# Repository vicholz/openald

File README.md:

# OpenALD v1.0

**OpenALD** is an open, rechargeable pocket FM radio: an ATmega328PB + RDA5807M (RRD-102 module) board that runs from one
18650 cell, charges and programs over USB-C, and lives in a 3D-printed 31.9 × 89.75 × 33.86 mm case (35.9 wide at its dock collar). The repo also
holds an **Adafruit Feather RP2040 variant** built from off-the-shelf boards, a printed **18650 case for the stock MI03
pocket radio**, and a **6-slot USB-C PD charging dock**. Since t116u (2026-11-24) the single-board and Feather radios share one dock interface: a
35.9 × 33.86 mm end footprint (t122u; was 31.9) with the **USB-C in the bottom end face, centred across the width, 6.62 mm behind the
front face, mouth 1.0 mm inside**. They stand upright in any dock pocket; **the MI03 keeps its side USB-C and is not
dock-compatible**. Everything is KiCad 9 + OpenSCAD, generated by Python scripts.

> **Status: designed, CAD- and datasheet-checked, NOT built and NOT hardware-validated.** ERC/DRC, the JLC placement
> check and the 3D case-fit checks pass, but no board has been built, powered or programmed. The only firmware is the Feather variant's Arduino sketch, which compiles but has never run on hardware; the single board still has none.
> Treat the first build of each part as a prototype (see the bring-up checklist in [HANDOFF.md](HANDOFF.md#8-hardware-bring-up-test-checklist)).

**Picking this up later (person or AI)? Start with [HANDOFF.md](HANDOFF.md)**: full design history, decisions, hard
constraints, open TODOs, test checklist and exact regeneration commands.

| Folder | What it is | Status |
|---|---|---|
| [`radio_single_board/`](radio_single_board/README.md) | **OpenALD v1.0** single-board radio: ATmega328PB + RDA5807M, CH340K USB-C programming, TP4056 ~900 mA charging with DW01A/FS8205A protection and reverse-cell protection, thumbwheel (press = battery check), slide switch, 3-LED level bar. **26.9 × 84.75 mm 2-layer PCB**; case **31.9 × 89.75 × 33.86 mm** (35.9-wide dock collar on its lowest 27 mm), USB-C centred in the bottom end | Designed; ERC/DRC/JLC-CPL/case fit pass; not built |
| [`charging_dock/`](charging_dock/README.md) | **OpenALD Dock v1.0**: 6 radios stand upright on their bottom-end USB-C in pockets recessed 25 mm into a flat top (3 × 2 aligned grid, 1 in apart, LED sight windows), any mix of single-board / Feather radios (**not the MI03**); one rear USB-C PD input (≥ 45 W charger, 15 V or 20 V); HUSB238 + 2 × SY8205 bucks + SY6280 limit per slot. **170.5 × 112.6 × 37.3 mm** (fits a 220 × 180 bed) | Designed; ERC/DRC/JLC-CPL/fit pass; not built |
| [`radio_adafruit_feather_rp2040/`](radio_adafruit_feather_rp2040/README.md) | **OpenALD Feather RP2040 v1.0**: Feather RP2040 + 27.25 mm FM module with jack + 18650 holder; **no PCB**: SIQ-02FVS3 wheel glued into a deck cradle, heat-staked SS-12F16 switch, FM module flipped on pegged standoffs, the Feather's own USB-C (bottom end) as the dock port, its CHG / red / NeoPixel LEDs visible through front-face holes, all hand-wired. Case **35.9 × 98.71 × 33.86 mm**, same dock interface as the single board | Designed; fit check pass; FM-module header/jack details assumed; not built |
| [`mi03_case/`](mi03_case/README.md) | 18650 case for the stock MI03 FM pocket radio, **27.5 × 89.75 × 34.83 mm**, USB-C on the left long side. **Not dock-compatible** | CAD only; fit check pass; not printed |

Dock ↔ radio mechanical contract: [`charging_dock/DOCK_INTERFACE.md`](charging_dock/DOCK_INTERFACE.md).

**Part colours (t124u):** every case family has its own hue so parts are easy to tell apart: single board **blues**,
Feather **greens**, MI03 **oranges / reds**, dock **purples** (legend in each README; `tools/palette.py`). Each case
also has a **coloured 3MF plate** next to its STLs (`*_colored.3mf`, one named, coloured object per part).
## Quick links
* Single-board radio: [Gerbers](radio_single_board/fab/openald-gerbers-jlcpcb.zip) · [JLC BOM](radio_single_board/fab/openald-BOM-jlcpcb.csv) · [JLC CPL](radio_single_board/fab/openald-CPL-jlcpcb.csv) · [human BOM](radio_single_board/fab/openald-BOM-human.csv) · [minimal (4-part) assembly set](radio_single_board/fab/minimal/) · [PCBWay BOM](radio_single_board/fab/openald-BOM-pcbway.xlsx) · [NextPCB BOM](radio_single_board/fab/openald-BOM-nextpcb.xls) · [schematic PDF](radio_single_board/docs/openald-schematic.pdf) · [case STLs](radio_single_board/case/)
* Dock: [Gerbers](charging_dock/fab/openald-dock-gerbers-jlcpcb.zip) · [JLC BOM](charging_dock/fab/openald-dock-BOM-jlcpcb.csv) · [JLC CPL](charging_dock/fab/openald-dock-CPL-jlcpcb.csv) · [human BOM](charging_dock/fab/openald-dock-BOM-human.csv) · [schematic PDF](charging_dock/docs/openald-dock-schematic.pdf) · [case STLs](charging_dock/case/)
* Feather variant: [BOM](radio_adafruit_feather_rp2040/docs/BOM.md) · [pin map](radio_adafruit_feather_rp2040/docs/pin_map.md) · [wiring diagram](radio_adafruit_feather_rp2040/docs/wiring_diagram.png) · [wiring schematic PDF](radio_adafruit_feather_rp2040/docs/wiring_schematic/openald-feather-wiring.pdf) · [firmware](radio_adafruit_feather_rp2040/firmware/) · [firmware notes](radio_adafruit_feather_rp2040/docs/firmware_notes.md) · [case STLs](radio_adafruit_feather_rp2040/case/)
* Ready-made zip packages per subproject: GitHub Release **v1.0** assets (or build them with `tools/make_packages.sh`).

## How to order (JLCPCB)
**Board settings for every board:** 2 layers, **1.6 mm** FR-4, **1 oz** copper, any colour, HASL lead-free (or ENIG),
**PCB Assembly: Economic, top side**. Upload the gerber zip from the subproject's `fab/`, then the `*-BOM-jlcpcb.csv` and
`*-CPL-jlcpcb.csv`. Use the centroid `.csv` or `.pos` only if a site asks for those formats.

* **Check every part's rotation in JLC's placement preview before paying.** The CPLs already contain per-part EasyEDA
  origin/rotation corrections (`JLC_CORR`, verified by `jlc_cpl_fit.py --check`), so the preview should be right; JLC
  engineers sometimes re-rotate by hand.
* Single-board radio: U4 (RRD-102 module), BT1 (18650 holder) and J3 (ISP pads, do not fit) are hand-solder/DNP.
  SW1 (SK-12E12-G5) is THT: choose Standard PCBA to have JLC fit it, or deselect it and hand-solder (5 joints).
  If the ATmega328PB (C132230) is low/out of stock, use **ATmega328P-AU (C14877)**, a drop-in (pick the 328P variant in MiniCore).
* **Minimal assembly option** (you have hot air/hotplate): upload the same gerbers with
  `radio_single_board/fab/minimal/openald-BOM-jlcpcb-minimal.csv` + `openald-CPL-jlcpcb-minimal.csv`. JLC places only
  J1 (USB-C), U1 (TP4056), U3 (ATmega328PB) and U7 (CH340K); buy the rest from LCSC with
  `fab/minimal/openald-LCSC-order-handsolder.csv` (5 boards + labelled spares). Order a separate **frameless** stencil
  (~$3) if you want one for hand paste.
* Dock: the six vertical USB-C plugs J2–J7 (HX TYPE C-M 16P V-SMT, **LCSC C55200592, low stock**) are hand-soldered; buy 7.
* Other vendors (PCBWay/NextPCB) have filled BOM templates, but **the CPL/placement files contain JLC-specific
  corrections**; generate a clean placement file before using another assembler (see HANDOFF §6).
* Cost figures in the docs are **estimates from published price tables (2026-11-10/11)**, not quotes.

## How to regenerate / check
Tested with: **KiCad 9.0.2** (`kicad-cli` + `pcbnew` Python module), **OpenSCAD 2021.01**, **Python 3.13**,
Freerouting (2026-10 build, Java 21+; run with OpenJDK 25) for re-routing only. Python packages: see
[`requirements.txt`](requirements.txt) (`pcbnew` comes with KiCad, not pip).

```bash
pip install -r requirements.txt
tools/fetch_kicad3d.sh && export KICAD9_3DMODEL_DIR=$PWD/tools/kicad3d   # stock KiCad STEP models for the fit checks
tools/check_all.sh            # ERC + DRC + JLC CPL check for all three boards (non-destructive, ~10 s)
tools/check_all.sh --case     # + rebuild cases and run the 3D fit checks (slow; rewrites STLs/previews)
```
Per subproject (details and expected results in [HANDOFF.md §7](HANDOFF.md#7-regeneration-and-checks)):
* `radio_single_board/scripts/run_all_pcb.sh` (full schematic → board → **re-route** → DRC; needs Freerouting),
  `python3 scripts/make_fab.py` / `--minimal`, `python3 scripts/make_vendor_boms.py`, `scripts/build_case.sh`.
* `charging_dock/scripts/run_all_pcb.sh`, `python3 scripts/make_fab.py`, `scripts/build_case.sh`.
* `radio_adafruit_feather_rp2040/make_all.sh` (everything) or `case/build_case.sh` (case only).
* `OPENALD_OFFLINE=1` makes `make_fab.py` reuse the saved `fab/lcsc_lookup.json` prices instead of querying JLC's parts API.
* `FREEROUTING=/path/freerouting.jar` and `JAVA=/path/java` override the router location (default `tools/freerouting.jar`, not in git).
* `EASYEDA_CACHE` overrides the EasyEDA footprint cache used by `jlc_cpl_fit.py` (default: the committed `tools/easyeda/`).

## Directory map
```
README.md            this file            HANDOFF.md        full resume / handoff document
LICENSE              CC0 1.0 Universal    requirements.txt  Python deps
tools/               check_all.sh, fetch_kicad3d.sh, make_packages.sh, easyeda/ (EasyEDA footprint cache for jlc_cpl_fit)
radio_single_board/  kicad/ fab/ (gerbers, JLC BOM/CPL, centroid, .pos, vendor BOMs, minimal/) case/ previews/ docs/ scripts/
charging_dock/       kicad/ fab/ case/ (STLs, floor_pads/) previews/ docs/ scripts/ DOCK_INTERFACE.md
mi03_case/           mi03_case.scad, stl/, previews/, scripts/ (MI03 radio case; the shared envelope's reference)
radio_adafruit_feather_rp2040/  case/ (STLs) previews/ docs/ scripts/ ref/ (Adafruit Eagle board, CC BY-SA) archive/ (retired PCB) make_all.sh
```

## License
Released into the public domain under **CC0 1.0 Universal** ([LICENSE](LICENSE)): hardware designs, scripts and docs.
Third-party reference files keep their own licenses (notably the Adafruit Feather RP2040 Eagle file in
`radio_adafruit_feather_rp2040/ref/`, CC BY-SA); see [HANDOFF.md §11](HANDOFF.md#11-license-and-third-party-files).

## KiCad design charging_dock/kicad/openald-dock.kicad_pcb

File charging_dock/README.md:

# OpenALD Dock v1.0 — 6-slot USB-C charging dock

A charging dock for six OpenALD radios (**3 columns × 2 rows, aligned grid**). It is designed
only for the **single-board and Feather radios**, which share one end footprint (35.9 W × 33.86 T since t122u) and one USB-C
position (**bottom end face, centred across the width, 6.62 mm behind the front face, mouth 1.0 mm inside**), so every
pocket takes either of them. **The MI03 radio is not dock-compatible** (Victor, 2026-11-24: "The mi03 version doesn't
need to work with the dock."); it keeps its side USB-C. A radio **stands upright on its bottom end**, front face toward
you, and drops onto a vertical USB-C plug in a pocket **recessed 25 mm into the flat top** of the dock. **One USB-C PD input at the rear** powers all six
slots.

> **Status: design only, nothing here is hardware-validated.** ERC/DRC are clean and the CAD fit check passes for both
> radios, but no board has been built, no charger tested, no part printed, and the plug height and insertion
> have not been measured on a real part. Treat the first build as a prototype.

The exact interface is in **[DOCK_INTERFACE.md](DOCK_INTERFACE.md)**.

**t116u redesign (2026-11-24, still v1.0):** both dockable radios now have their USB-C on the **bottom end**, so the
radios stand upright again (the earlier 2026-11-24 version had them lying on a side-mounted USB-C in 216.9 × 174.79 ×
26.3 mm). Pockets are 31.9 × 33.86 (+0.35 mm per side) with **50.8 mm walls** on the back and both sides; the front
wall is open above a 2.5 mm lip except for 5 mm corner returns, so the front faces (single-board level bar and charge
LEDs, Feather CHG LED and NeoPixel) stay visible. The right pocket wall has a notch at the front
above 30 mm for the single-board radio's switch knob and wheel. Same electronics and schematic; the PCB was re-placed
and re-routed for the new plug positions.

**t120u (2026-11-24, still v1.0):** Victor: "make the slots so they are in a grid and not offset." The back row now
stands directly behind the front row (aligned 3 × 2 grid), which shrinks the dock to **158.5 × 112.62 × 63.1 mm**
(PCB 152.70 × 106.82, re-placed and re-routed). Trade-off: front faces of back-row radios are hidden behind the
front-row radios unless you look down from steeply above (see *Feather LEDs in the dock* below).

**t121u (2026-11-24, still v1.0): flat dock.** Victor: "Remove the tall guides on the dock. The dock should be flat
with recessed square holes that are 2-4cm deep to act as a guide." The 50.8 mm pocket walls, front lips and corner
returns are gone: the dock is a closed **158.5 × 112.62 × 37.3 mm** box with six pockets **25 mm deep** in its flat
top (same aligned grid, same PCB, pads and plug height). The Feather's LEDs (4 and 20 mm above the floor) would sit
below the top, so each pocket's front wall has a **20 mm sight window** down to 2 mm above the floor: front row
straight out through the dock's front face, back row into a closed trench in the top whose floor rises at 50° toward
the front row. No side notch: both radios' switch knobs and wheels sit above 25 mm.

**t122u (2026-11-24, still v1.0): 35.9 mm pockets.** Victor asked for 2 mm more room on each side of the Feather in
its case, so the Feather case is now 35.9 wide. The pockets are **35.9 × 33.86** (+0.35/side). The single-board case
keeps its 31.9 body but has a 35.9-wide **dock collar** on its lowest 27 mm, so both radios still share one end
footprint. The 25.4 mm gap between radios stays, so the dock is **170.5 × 112.62 × 37.3 mm** (still fits 220 × 180).
The PCB is now **164.70 × 106.82**, with the plugs re-placed at the new pocket centres and re-routed (ERC 0/0, DRC 0
errors / 0 unconnected / 72 silk-only, CPL OK). Fit check: 0 interferences, both radios, all six pockets.

## Key numbers
| | |
|---|---|
| Outer size | **170.5 × 112.62 × 37.3 mm** (W × D × H; flat top) — **fits a 220 × 180 bed** |
| Layout | 3 × 2 aligned grid, **25.4 mm (1.0 in)** between radios in X and Y; margins 6 sides/front, 13.5 back |
| Pocket | 35.9 × 33.86 + 0.35/side, **recessed 25.0 mm** (floor Z 12.3, top Z 37.3, 1.5 mm lead-in chamfer); 20 mm sight window in the front wall from 2 mm above the floor (back row: sloped trench, 50°); no side notch |
| Plug | HX TYPE C-M 16P vertical, top Z 19.3 → **6.0 mm past the radio's receptacle mouth** (both radios; full seat 6.20 ± 0.20) |
| Floor pads | 4.6 mm (`PAD_T`), one per slot |
| PCB | **164.70 × 106.82 mm**, 2-layer, 1.6 mm, all SMT parts on top |
| Minimum charger | **USB-C PD, 45 W: must offer 20 V ≥ 2.25 A or 15 V ≥ 3 A** |
| Per-slot limit | ~1.45 A (1.09–1.81 A, SY6280 ±25 %), 5.10 V |
| Filament | solid volumes: top shell 102.5 cm³, base 43.6 cm³, 6 pads 41.7 cm³ (~233 g PLA if solid, less with infill) |
| Docked radios | single-board 89.75 mm tall, Feather 98.71 mm tall above the pocket floor (tops at Z 102 / 111) |

## Part colours (t124u)
Victor: "make all 3 cases and their parts different colors so it is easy to tell the parts apart". Each case family has
its own hue (single board **blues**, Feather **greens**, MI03 **oranges / reds**, dock **purples**); this one uses
**purples**. The same colours are used in every preview and in the coloured 3MF plate **`case/openald_dock_colored.3mf`** (all printed parts laid
out on one plate, each a separate named object with its colour; source `../tools/palette.py`, rebuilt by
`../tools/make_3mf.py`). Colours are only for telling the parts apart; print in any filament.

| Part (STL) | What | Colour | Hex |
|---|---|---|---|
| `case/dock_top_shell.stl` | top shell | purple | `#7B4FB8` |
| `case/dock_base.stl` | base | lavender | `#C9B6E8` |
| `case/dock_floor_pads_x6.stl` | floor pads (x6) | dark purple | `#3B2360` |

## Power architecture
```
USB-C IN (J1, HRO TYPE-C-31-M-12, CC1/CC2 -> HUSB238)
  -> F1 4 A fuse (0466004.NRHF) -> D1 SMBJ22A TVS -> C1 10 uF 50 V
  -> Q1 AO4407A P-FET input switch (gate: R2 100k / R3 47k / C3 4.7 nF soft turn-on, driven by HUSB238 GATE; opens on OVP)
  -> VIN_SW, C4 100 uF 35 V
     -> U2 SY8205FCC buck A (4.7 uH MWSA0604S, 3x22 uF + 470 uF, 75k/10k -> 5.10 V) -> slots 1, 2, 4
     -> U3 SY8205FCC buck B (same)                                                   -> slots 3, 5, 6
        each slot: SY6280AAC current-limited switch (Rset 4.7k -> ~1.45 A) + 10 uF -> vertical plug VBUS,
        22k Rp on CC ("default USB power" to the radio's 5.1k Rd), plug GND + shell to GND
Status LED (light pipe in the top, in the back-row gap between slots 4 and 5): green = 5 V up; red = input present but no usable PD
```
* **HUSB238** (VSET open = request up to 20 V, ISET 13.7k = 2.25 A) picks the highest PDO ≤ 20 V that offers ≥ 2.25 A,
  otherwise it steps down. D+/D− are left open (PD only).
* **Buck enable threshold:** EN divider 100k/12k from VIN_SW. The bucks turn on at 11.2–13.1 V (typ. 12.1 V). **5 V and
  9 V never enable them** (non-PD or 5 V-only chargers are safe: the dock stays off with the red LED lit). 15 V and
  20 V always enable them. **12 V-only chargers are not supported** (they may or may not start).
* Worst-case load is 6 × ~0.95 A × 5.1 V ≈ 29 W. At 20 V/2.25 A (45 W) there is about 35 % headroom after converter
  losses. Each buck is rated 5 A and carries ≤ 3 radios.

| Part | LCSC | Stock (2026-11-11 PST) | Unit |
|---|---|---|---|
| HUSB238_002DD PD sink | C7471904 | 17,771 | $0.47 |
| SY8205FCC buck ×2 | C111875 | 10,557 | $0.34 |
| SY6280AAC slot switch ×6 | C55136 | 97,877 | $0.09 |
| AO4407A input P-FET | C16072 | 19,166 | $0.33 |
| MWSA0604S-4R7MT 4.7 µH 7 A ×2 | C408457 | 8,136 | $0.17 |
| 0466004.NRHF 4 A fuse | C187596 | 14,764 | $0.08 |
| SMBJ22A TVS | C151920 | 7,664 | $0.07 |
| 100 µF 35 V / 470 µF 10 V electrolytic | C2895269 / C2858856 | 5,149 / 138,705 | $0.12 / $0.05 |
| HRO TYPE-C-31-M-12 input receptacle | C165948 | 281,637 | $0.19 |
| HX TYPE C-M 16P V-SMT vertical plug ×6 (hand solder) | C55200592 | **782** | $0.54 |

The full list is in `fab/openald-dock-BOM-human.csv` (live stock and price); `fab/cost_estimate.txt` has the cost estimate.

## Files
| Path | What |
|---|---|
| `kicad/openald-dock.kicad_{pro,sch,pcb}` | KiCad 9 project (schematic and board are generated by the scripts) |
| `fab/openald-dock-gerbers-jlcpcb.zip` | Gerbers + drill (JLCPCB) |
| `fab/openald-dock-BOM-jlcpcb.csv`, `fab/openald-dock-CPL-jlcpcb.csv` | JLC assembly BOM + CPL (JLC_CORR rotation/offset corrections applied) |
| `fab/openald-dock-centroid.csv`, `fab/openald-dock.pos` | Centroid / KiCad position files |
| `fab/openald-dock-BOM-human.csv`, `fab/cost_estimate.txt`, `fab/lcsc_lookup.json` | Human BOM with live stock and prices, cost estimate |
| `fab/erc_report.txt`, `fab/drc_report.txt`, `fab/jlc_cpl_fit.json` | Check reports |
| `case/openald_dock.scad`, `case/dock_params.scad` | OpenSCAD case (parameters generated from the PCB layout) |
| `case/dock_top_shell.stl`, `case/dock_base.stl`, `case/dock_floor_pads_x6.stl`, `case/floor_pads/*.stl` | Print-ready STLs (already in print orientation) |
| `case/dock_fit_report.txt` | Fit-check result (all three radio cases, real STLs, every slot) |
| `docs/openald-dock-schematic.pdf`, `previews/*.png` | Schematic PDF, PCB/case renders, CPL overlay plots |
| `scripts/` | Generators: `run_all_pcb.sh` (symbols → schematic → ERC → board → route → post-route → DRC), `make_fab.py`, `jlc_cpl_fit.py`, `build_case.sh`, `check_dock_fit.py`, `render_pcb_previews.py`; `geom.py` is the single source of the geometry |

## Checks (t116u, 2026-11-24)
* **ERC:** 0 errors, 0 warnings.
* **DRC:** 0 errors, **0 unconnected**. 72 silkscreen-only warnings (2 silk_edge_clearance, 39 silk_over_copper, 31 silk_overlap; cosmetic).
* **JLC placement:** `jlc_cpl_fit.py --check` → *correction table: OK*. Overlays in `previews/cpl_overlay_*.png`.
* **Case fit** (`scripts/check_dock_fit.py` → `case/dock_fit_report.txt`): **INTERFERENCES: 0**. It exports the real
  STLs of both radio cases (single board, Feather) plus what sticks out of them (single-board switch knob in both
  positions and wheel; Feather wheel and switch knob), stands each in every one of the six pockets and checks it
  against the shell, base, pads and plug; **sweeps the insertion path** (radio lowered straight down from above the
  top); checks the PCB and its 80 part boxes against every case part; and the case parts against each other.
  Smallest plug-to-case gap 0.32 mm (both radios); plug centred on the radio's USB opening. Closest PCB part to the
  shell: D2, 0.19 mm (part boxes). All printed STLs are watertight single bodies
  (`dock_floor_pads_x6.stl` is six bodies on purpose).
* **Feather LEDs in the dock** (rays at 0/15/30/45/60/75° upward from the CHG (≈ 4 mm above the floor), red (≈ 4 mm)
  and NeoPixel (≈ 20 mm) holes through the sight windows, tested against the shell and radios in the other five
  pockets). The single-board radio's level bar and charge LEDs sit ~77–82 mm up, well above the top.
  * **Front row, slots 1–3: clear at every angle (0–75°)**, including level, through the front windows.
  * **Back row, slots 4–6 with radios in the front row: blocked 0–60°, visible from about 75° up.** Removing the
    walls did not change this: the blocker is the front-row radio itself (64–74 mm above the top, 25.4 mm in
    front), which needs about 74° to look over. **With the front pocket empty**, the dock alone lets you see the
    CHG / red LEDs from 60° and the NeoPixel from 15°. Reported as `info`, not failures. Fix if needed (not built):
    a stepped back row (back pockets ≈ 60 mm higher for a ~45° view) or a much deeper gap between rows.
* Previews: `previews/dock_assembly.png`, `dock_assembly_rear.png`, `dock_exploded.png`, `dock_top_view.png`
  (aligned grid), `dock_front_view.png`, `dock_print_layout.png`, `dock_plug_insertion_per_radio.png`
  (both radios on their plugs), PCB renders.

## Printing (no supports)
* **Top shell:** print it **upside down, flat top on the bed**, as exported. Pocket walls, bosses, light pipe and the
  window blocks grow straight up; the back-row trench floors overhang at 40° from vertical; the only bridges are the
  20 mm front-window sills and the short vents / rear USB-C opening.
* **Base:** print it flat, as exported.
* **Floor pads (6):** print them as exported (one STL per slot in `floor_pads/`, or all six in `dock_floor_pads_x6.stl`).
* PETG or PLA, 0.2 mm layers, 3 walls. Try one radio in one pocket before printing all six pads. If the fit is tight,
  the guide clearance is `CLR_GUIDE` in `scripts/geom.py`.

## Assembly
1. **Order the PCB** with JLC SMT assembly (gerber zip + BOM + CPL). The six vertical plugs J2–J7 are **not** in the JLC
   BOM (LCSC has no EasyEDA footprint for C55200592). Buy 6 (+1 spare) and hand-solder them: 16 fine-pitch (0.8 mm)
   SMD pads plus 2 plated shell slots; use flux, a fine tip or hot air, and keep each plug **vertical** (a printed
   floor pad slipped over it works as a jig).
2. **Test before docking a radio:** with a ≥ 45 W PD charger, green lights and red stays off; each slot reads
   5.0–5.2 V on VBUS. A 5 V-only charger gives red only, no slot voltage.
3. Press 6 M3 heat-set inserts into the shell bosses. Lay the PCB on the base standoffs, drop the six floor pads in
   (pegs into the PCB holes), lower the shell over everything and fit 6 × **M3 × 10** screws from below.
4. Stand a radio in a pocket **USB-C end down, front face toward you**, and press it down onto the plug.

## Open risks and judgment calls
* **Plug height and insertion are not measured.** The HX drawing gives 11.60 (used here, 6.0 mm insertion) but also a
  12.50 overall. Measure a soldered plug from the PCB top; if it is taller, make `PAD_T` thicker by the difference in
  `scripts/geom.py` and rebuild.
* **Receptacle depth:** the real seat depth of the radios' receptacles isn't on their drawings; 6.20 ± 0.20 is the
  USB-C spec value. Both radios have the mouth 1.0 mm inside the bottom end face.
* **Tall radios on a plug:** the 25 mm deep pocket (0.35 mm clearance, ≤ ~1.6° tilt) takes side loads, not the plug;
  the radio guides for 18 mm before the plug tip reaches its opening, and its top stands 65–74 mm above the dock.
  Lift straight up.
* **Older radios** (side USB-C, 89.75 × 34.83, or the original end-USB 43 × 92 boards) **do not fit** this dock.
* **Hand-soldered plugs:** fine pitch, must be perpendicular; ~0.5 mm misalignment tolerance.
* **Plug supply:** only 782 in stock at LCSC when checked. Buy spares early.
* **12 V fallback:** 12 V-only chargers are deliberately not supported.
* **Autorouted power layout:** Freerouting plus scripted widening of high-current tracks and GND pours on both
  layers. Review the buck hot loops in `previews/pcb_*.png` before ordering.
* **Heat:** six radios charging upright in recessed pockets, no fan; the top and skirt are vented over the bucks. Watch
  radio temperature on the first full charge.
* **While docked:** the single-board level bar and charge LEDs are well above the top; the Feather CHG / red LEDs and
  NeoPixel show through the 20 mm sight windows (back row only from steeply above, see above). Both radios' switches
  and wheels sit above the 25 mm pockets.
* **Not validated:** HUSB238 negotiation, buck stability, SY6280 limits, thermals and plug mating are all untested.

## History
* v1.0 (2026-11-11): first design (radios standing USB-down, 191.8 × 111.7 × 62.5 mm). The project was renamed from
  OpenALS to OpenALD before release, so the dock was born as "OpenALD Dock v1.0".
* 2026-11-12: floor pads 3.1 → 4.0, standoffs 5.0 → 4.1 for 6.0 mm insertion.
* 2026-11-24 (still v1.0): unified radio envelope; radios lie on the USB-C side; 2 × 3 layout, 216.9 × 174.79 ×
  26.3 mm, PCB 211.1 × 169.0, pads 4.6; fit-checked with all three radios.
* 2026-11-24 (still v1.0): single-board radio widened to 30.5 (2-layer board), re-checked. MI03 support dropped
  (Victor: "The mi03 version doesn't need to work with the dock."): fit check, previews and the insertion plot cover
  the single-board and Feather radios only. Pocket geometry, outer size and PCB unchanged (both radios share the same
  89.75 × 34.83 footprint, so dropping the MI03 frees nothing).
* t116u (2026-11-24, still v1.0): USB-C moved to the **bottom end** of both dockable radios (centred, 6.62 behind the
  front face). Radios stand upright again: 3 + 3 staggered pockets, 50.8 mm walls with a front window, 187.15 ×
  112.62 × 63.1 mm (fits 220 × 180), PCB 181.35 × 106.82 re-placed and re-routed (DRC 0, ERC 0, CPL OK). Fit check
  adds the insertion sweep, the radios' protruding knobs/wheels and a Feather-LED line-of-sight test.
* t120u (2026-11-24, still v1.0): aligned 3 × 2 grid (Victor: "make the slots so they are in a grid and not offset").
  158.5 × 112.62 × 63.1 mm (fits 220 × 180), PCB 152.70 × 106.82 re-placed (LEDs, light pipe and C4 in the back-row
  gap 4–5; title and a screw in gap 5–6) and re-routed: ERC 0/0, DRC 0 err / 0 unconnected / 72 silk, CPL OK. Fit
  check 0 interferences, both radios, all six pockets; back-row Feather LEDs visible only from ~75° up (front row clear).
* t121u (2026-11-24, still v1.0): flat dock (Victor: "Remove the tall guides on the dock. The dock should be flat with
  recessed square holes that are 2-4cm deep"). 158.5 × 112.62 × **37.3** mm (was 63.1 tall), pockets recessed 25 mm,
  20 mm sight windows (front) / sloped trenches (back) for the Feather LEDs, no side notch, raised housings dropped
  (27 mm room under the top), shell printed upside down. PCB, pads and plug height unchanged (DRC/ERC/CPL as t120u).
  Fit check 0 interferences, both radios, all six pockets, insertion sweep.
* t122u (2026-11-24, still v1.0): pockets 35.9 wide for the wider Feather case (single-board case: 35.9 dock collar).
  170.5 × 112.62 × 37.3 mm, PCB 164.70 × 106.82 re-placed and re-routed: ERC 0/0, DRC 0 err / 0 unconnected / 72 silk,
  CPL OK. Fit check 0 interferences; Feather LED visibility unchanged (front row clear 0–75°, back row from ~75°).

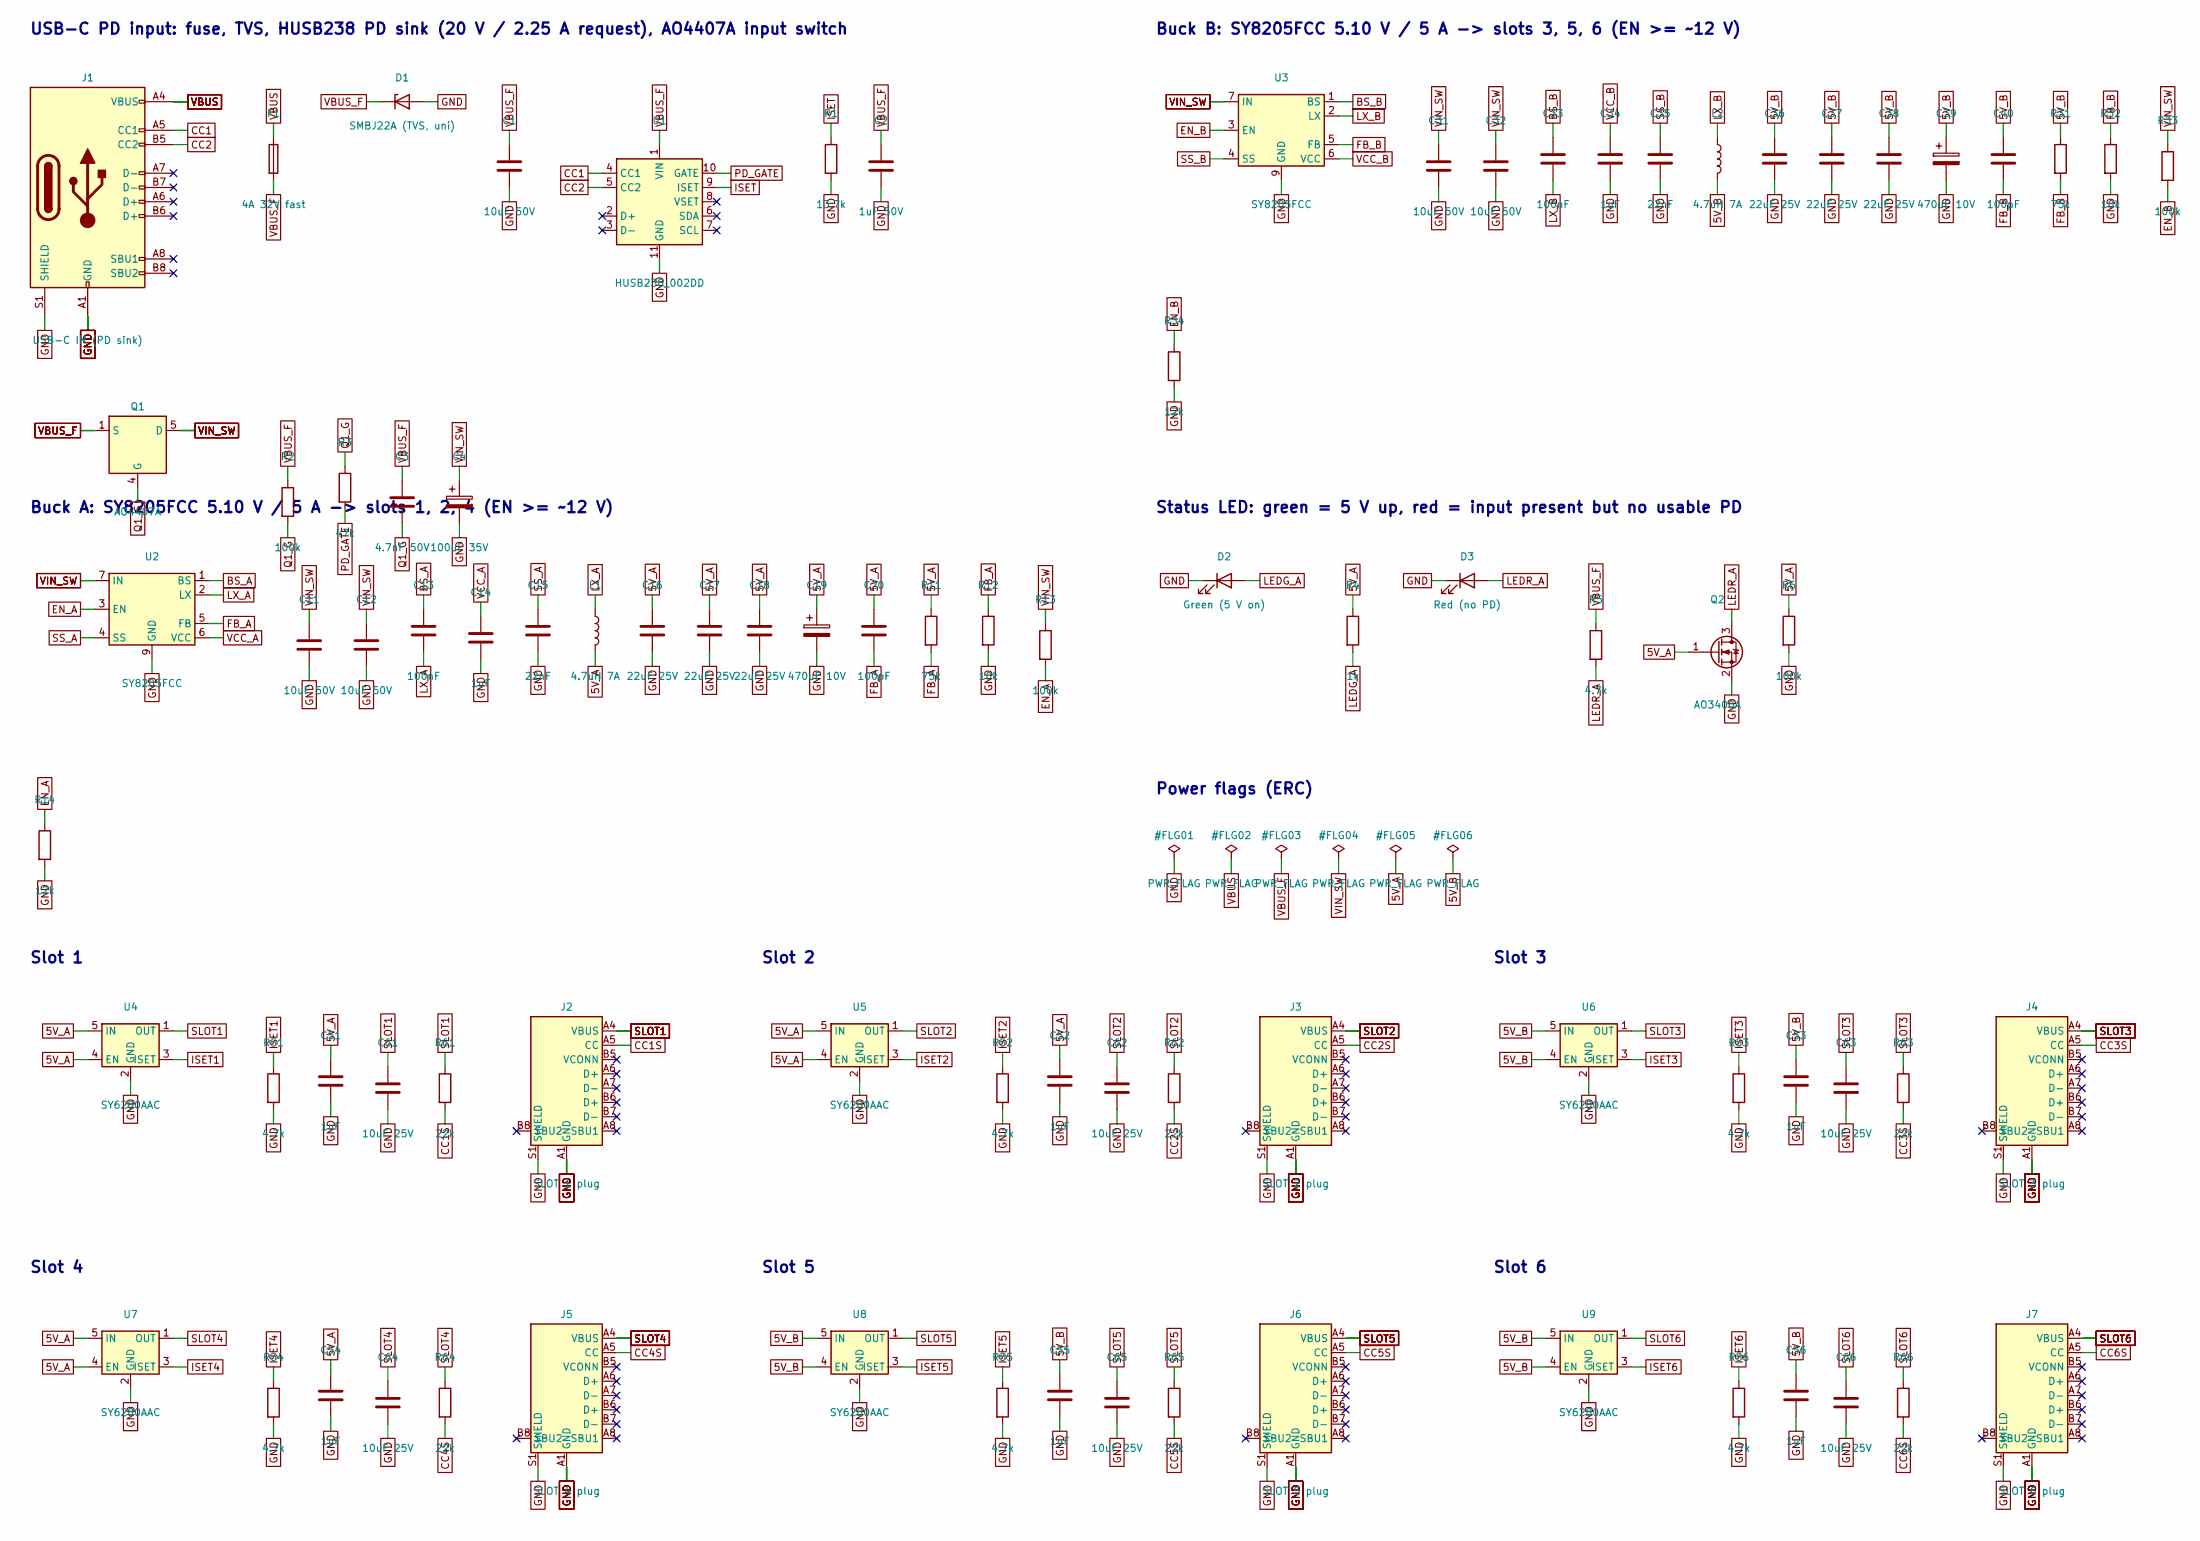
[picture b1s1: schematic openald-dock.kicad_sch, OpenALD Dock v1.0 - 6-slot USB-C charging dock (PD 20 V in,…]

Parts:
C1, C11, C12, C31, C32: 10uF 50V; C_1206_3216Metric; MPN CL31A106KBHNNNE; LCSC C13585
C2: 1uF 50V; C_0603_1608Metric; MPN CL10A105KB8NNNC; LCSC C15849
C3: 4.7nF 50V; C_0603_1608Metric; MPN 0603B472K500NT; LCSC C53987
C4: 100uF 35V; CP_Elec_8x10; MPN RVE100UF35V67RV0161; LCSC C2895269
C13, C33: 100nF; C_0603_1608Metric; MPN CC0603KRX7R9BB104; LCSC C14663
C14, C34, C51, C52, C53, C54, C55, C56: 1uF; C_0603_1608Metric; MPN CL10A105KB8NNNC; LCSC C15849
C15, C35: 22nF; C_0603_1608Metric; MPN CL10B223KB8NNNC; LCSC C21122
C16, C17, C18, C36, C37, C38: 22uF 25V; C_0805_2012Metric; MPN CL21A226MAQNNNE; LCSC C45783
C19, C39: 470uF 10V; CP_Elec_6.3x7.7; MPN RVT470UF10V67RV0159; LCSC C2858856
C20, C40: 100pF; C_0603_1608Metric; MPN CL10C101JB8NNNC; LCSC C14858
C61, C62, C63, C64, C65, C66: 10uF 25V; C_0805_2012Metric; MPN CL21A106KAYNNNE; LCSC C15850
D1: SMBJ22A (TVS, uni); D_SMB; MPN SMBJ22A; LCSC C151920
D2: Green (5 V on); LED_0603_1608Metric; MPN KT-0603G; LCSC C12624
D3: Red (no PD); LED_0603_1608Metric; MPN KT-0603R; LCSC C2286
F1: 4A 32V fast; Fuse_1206_3216Metric; MPN Littelfuse 0466004.NRHF; LCSC C187596
J1: USB-C IN (PD sink); USB_C_Receptacle_HRO_TYPE-C-31-M-12; MPN HRO TYPE-C-31-M-12; LCSC C165948
J2: SLOT 1 plug; USB_C_Plug_HX_TYPE-C-M-16P_Vertical; MPN HX TYPE C-M 16P V-SMT; LCSC C55200592
J3: SLOT 2 plug; USB_C_Plug_HX_TYPE-C-M-16P_Vertical; MPN HX TYPE C-M 16P V-SMT; LCSC C55200592
J4: SLOT 3 plug; USB_C_Plug_HX_TYPE-C-M-16P_Vertical; MPN HX TYPE C-M 16P V-SMT; LCSC C55200592
J5: SLOT 4 plug; USB_C_Plug_HX_TYPE-C-M-16P_Vertical; MPN HX TYPE C-M 16P V-SMT; LCSC C55200592
J6: SLOT 5 plug; USB_C_Plug_HX_TYPE-C-M-16P_Vertical; MPN HX TYPE C-M 16P V-SMT; LCSC C55200592
J7: SLOT 6 plug; USB_C_Plug_HX_TYPE-C-M-16P_Vertical; MPN HX TYPE C-M 16P V-SMT; LCSC C55200592
L1, L2: 4.7uH 7A; L_Sunlord_MWSA0604S; MPN Sunlord MWSA0604S-4R7MT; LCSC C408457
Q1: AO4407A; SOIC-8_3.9x4.9mm_P1.27mm; MPN AOS AO4407A; LCSC C16072
Q2: AO3400A; SOT-23; MPN AOS AO3400A; LCSC C20917
R1: 13.7k; R_0603_1608Metric; MPN 0603WAF1372T5E; LCSC C22793
R2, R6, R13, R33: 100k; R_0603_1608Metric; MPN 0603WAF1003T5E; LCSC C25803
R3: 47k; R_0603_1608Metric; MPN 0603WAF4702T5E; LCSC C25819
R4: 1k; R_0603_1608Metric; MPN 0603WAF1001T5E; LCSC C21190
R5: 4.7k; R_0805_2012Metric; MPN 0805W8F4701T5E; LCSC C17673
R11, R31: 75k; R_0603_1608Metric; MPN 0603WAF7502T5E; LCSC C23242
R12, R32: 10k; R_0603_1608Metric; MPN 0603WAF1002T5E; LCSC C25804
R14, R34: 12k; R_0603_1608Metric; MPN 0603WAF1202T5E; LCSC C22790
R51, R52, R53, R54, R55, R56: 4.7k; R_0603_1608Metric; MPN 0603WAF4701T5E; LCSC C23162
R61, R62, R63, R64, R65, R66: 22k; R_0603_1608Metric; MPN 0603WAF2202T5E; LCSC C31850
U1: HUSB238_002DD; DFN-10-1EP_3x3mm_P0.5mm_EP1.55x2.48mm; MPN Hynetek HUSB238_002DD; LCSC C7471904
U2, U3: SY8205FCC; SOIC-8-1EP_3.9x4.9mm_P1.27mm_EP2.29x3mm; MPN Silergy SY8205FCC; LCSC C111875
U4, U5, U6, U7, U8, U9: SY6280AAC; SOT-23-5; MPN Silergy SY6280AAC; LCSC C55136

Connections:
5V_A: C16.1, C17.1, C18.1, C19.1, C20.1, C51.1, C52.1, C54.1, L1.2, Q2.1 (G), R4.1, R6.1, R11.1, U4.4 (EN), U4.5 (IN), U5.4 (EN), U5.5 (IN), U7.4 (EN), U7.5 (IN)
5V_B: C36.1, C37.1, C38.1, C39.1, C40.1, C53.1, C55.1, C56.1, L2.2, R31.1, U6.4 (EN), U6.5 (IN), U8.4 (EN), U8.5 (IN), U9.4 (EN), U9.5 (IN)
BS_A: C13.1, U2.1 (BS)
BS_B: C33.1, U3.1 (BS)
CC1: J1.A5 (CC1), U1.4 (CC1)
CC1S: J2.A5 (CC), R61.2
CC2: J1.B5 (CC2), U1.5 (CC2)
CC2S: J3.A5 (CC), R62.2
CC3S: J4.A5 (CC), R63.2
CC4S: J5.A5 (CC), R64.2
CC5S: J6.A5 (CC), R65.2
CC6S: J7.A5 (CC), R66.2
EN_A: R13.2, R14.1, U2.3 (EN)
EN_B: R33.2, R34.1, U3.3 (EN)
FB_A: C20.2, R11.2, R12.1, U2.5 (FB)
FB_B: C40.2, R31.2, R32.1, U3.5 (FB)
GND: C1.2, C2.2, C4.2, C11.2, C12.2, C14.2, C15.2, C16.2, C17.2, C18.2, C19.2, C31.2, C32.2, C34.2, C35.2, C36.2, C37.2, C38.2, C39.2, C51.2, C52.2, C53.2, C54.2, C55.2, C56.2, C61.2, C62.2, C63.2, C64.2, C65.2, C66.2, D1.2 (A), D2.1 (K), D3.1 (K), J1.A1 (GND), J1.A12 (GND), J1.B1 (GND), J1.B12 (GND), J1.S1 (SHIELD), J2.A1 (GND), J2.A12 (GND), J2.B1 (GND), J2.B12 (GND), J2.S1 (SHIELD), J3.A1 (GND), J3.A12 (GND), J3.B1 (GND), J3.B12 (GND), J3.S1 (SHIELD), J4.A1 (GND), J4.A12 (GND), J4.B1 (GND), J4.B12 (GND), J4.S1 (SHIELD), J5.A1 (GND), J5.A12 (GND), J5.B1 (GND), J5.B12 (GND), J5.S1 (SHIELD), J6.A1 (GND), J6.A12 (GND), J6.B1 (GND), J6.B12 (GND), J6.S1 (SHIELD), J7.A1 (GND), J7.A12 (GND), J7.B1 (GND), J7.B12 (GND), J7.S1 (SHIELD), Q2.2 (S), R1.2, R6.2, R12.2, R14.2, R32.2, R34.2, R51.2, R52.2, R53.2, R54.2, R55.2, R56.2, U1.11 (GND), U2.9 (GND), U3.9 (GND), U4.2 (GND), U5.2 (GND), U6.2 (GND), U7.2 (GND), U8.2 (GND), U9.2 (GND)
ISET: R1.1, U1.9 (ISET)
ISET1: R51.1, U4.3 (ISET)
ISET2: R52.1, U5.3 (ISET)
ISET3: R53.1, U6.3 (ISET)
ISET4: R54.1, U7.3 (ISET)
ISET5: R55.1, U8.3 (ISET)
ISET6: R56.1, U9.3 (ISET)
LEDG_A: D2.2 (A), R4.2
LEDR_A: D3.2 (A), Q2.3 (D), R5.2
LX_A: C13.2, L1.1, U2.2 (LX)
LX_B: C33.2, L2.1, U3.2 (LX)
PD_GATE: R3.2, U1.10 (GATE)
Q1_G: C3.2, Q1.4 (G), R2.2, R3.1
SLOT1: C61.1, J2.A4 (VBUS), J2.A9 (VBUS), J2.B4 (VBUS), J2.B9 (VBUS), R61.1, U4.1 (OUT)
SLOT2: C62.1, J3.A4 (VBUS), J3.A9 (VBUS), J3.B4 (VBUS), J3.B9 (VBUS), R62.1, U5.1 (OUT)
SLOT3: C63.1, J4.A4 (VBUS), J4.A9 (VBUS), J4.B4 (VBUS), J4.B9 (VBUS), R63.1, U6.1 (OUT)
SLOT4: C64.1, J5.A4 (VBUS), J5.A9 (VBUS), J5.B4 (VBUS), J5.B9 (VBUS), R64.1, U7.1 (OUT)
SLOT5: C65.1, J6.A4 (VBUS), J6.A9 (VBUS), J6.B4 (VBUS), J6.B9 (VBUS), R65.1, U8.1 (OUT)
SLOT6: C66.1, J7.A4 (VBUS), J7.A9 (VBUS), J7.B4 (VBUS), J7.B9 (VBUS), R66.1, U9.1 (OUT)
SS_A: C15.1, U2.4 (SS)
SS_B: C35.1, U3.4 (SS)
VBUS: F1.1, J1.A4 (VBUS), J1.A9 (VBUS), J1.B4 (VBUS), J1.B9 (VBUS)
VBUS_F: C1.1, C2.1, C3.1, D1.1 (K), F1.2, Q1.1 (S), Q1.2 (S), Q1.3 (S), R2.1, R5.1, U1.1 (VIN)
VCC_A: C14.1, U2.6 (VCC)
VCC_B: C34.1, U3.6 (VCC)
VIN_SW: C4.1, C11.1, C12.1, C31.1, C32.1, Q1.5 (D), Q1.6 (D), Q1.7 (D), Q1.8 (D), R13.1, R33.1, U2.7 (IN), U2.8 (IN), U3.7 (IN), U3.8 (IN)

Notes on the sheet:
USB-C PD input: fuse, TVS, HUSB238 PD sink (20 V / 2.25 A request), AO4407A input switch
Buck A: SY8205FCC 5.10 V / 5 A -> slots 1, 2, 4 (EN >= ~12 V)
Buck B: SY8205FCC 5.10 V / 5 A -> slots 3, 5, 6 (EN >= ~12 V)
Status LED: green = 5 V up, red = input present but no usable PD
Slot 1
Slot 2
Slot 3
Slot 4
Slot 5
Slot 6
Power flags (ERC)

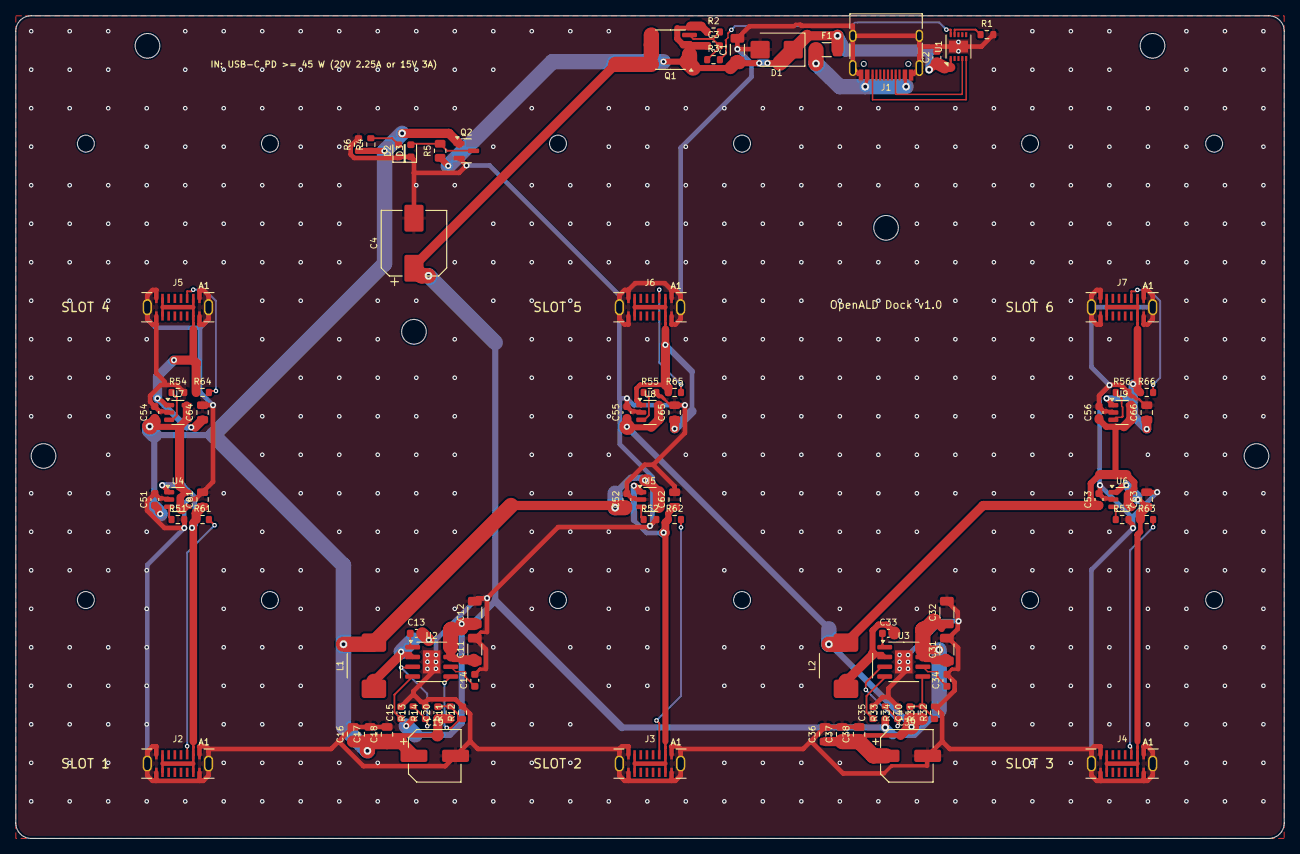
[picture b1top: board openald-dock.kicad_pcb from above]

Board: 2 copper layers, 164.7 x 106.8 mm, 104 parts (0 on the bottom side), 43 nets.

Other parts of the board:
H1, H2, H3, H4, H5, H6: M3; MountingHole_3.2mm_M3
H7, H8, H9, H10, H11, H12, H13, H14, H15, H16, H17, H18: peg; MountingHole_2.2mm_M2

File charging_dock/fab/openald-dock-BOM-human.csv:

Designator(s),Qty/board,Value / description,Manufacturer part,LCSC #,JLC library,LCSC stock (live),Unit price USD (qty 10),Assembly,Link
J1,1,USB-C IN (PD sink) (USB_C_Receptacle_HRO_TYPE-C-31-M-12),HRO TYPE-C-31-M-12,C165948,Extended,281647,0.1868,JLCPCB SMT,https://www.lcsc.com/product-detail/C165948.html
F1,1,4A 32V fast (Fuse_1206_3216Metric),Littelfuse 0466004.NRHF,C187596,Extended,14764,0.0848,JLCPCB SMT,https://www.lcsc.com/product-detail/C187596.html
D1,1,"SMBJ22A (TVS, uni) (D_SMB)",SMBJ22A,C151920,Extended,7664,0.0684,JLCPCB SMT,https://www.lcsc.com/product-detail/C151920.html
"C1,C11,C12,C31,C32",5,10uF 50V (C_1206_3216Metric),CL31A106KBHNNNE,C13585,Basic,3495621,0.127,JLCPCB SMT,https://www.lcsc.com/product-detail/C13585.html
U1,1,HUSB238_002DD (DFN-10-1EP_3x3mm_P0.5mm_EP1.55x2.48mm),Hynetek HUSB238_002DD,C7471904,Extended,17771,0.4695,JLCPCB SMT,https://www.lcsc.com/product-detail/C7471904.html
R1,1,13.7k (R_0603_1608Metric),0603WAF1372T5E,C22793,Extended,156335,0.0022,JLCPCB SMT,https://www.lcsc.com/product-detail/C22793.html
"C2,C14,C34,C51,C52,C53,C54,C55,C56",9,1uF 50V / 1uF (C_0603_1608Metric),CL10A105KB8NNNC,C15849,Basic,14039417,0.0113,JLCPCB SMT,https://www.lcsc.com/product-detail/C15849.html
Q1,1,AO4407A (SOIC-8_3.9x4.9mm_P1.27mm),AOS AO4407A,C16072,Extended,19166,0.3312,JLCPCB SMT,https://www.lcsc.com/product-detail/C16072.html
"R2,R6,R13,R33",4,100k (R_0603_1608Metric),0603WAF1003T5E,C25803,Basic,15176547,0.0029,JLCPCB SMT,https://www.lcsc.com/product-detail/C25803.html
R3,1,47k (R_0603_1608Metric),0603WAF4702T5E,C25819,Basic,2904329,0.0016,JLCPCB SMT,https://www.lcsc.com/product-detail/C25819.html
C3,1,4.7nF 50V (C_0603_1608Metric),0603B472K500NT,C53987,Basic,809197,0.0052,JLCPCB SMT,https://www.lcsc.com/product-detail/C53987.html
C4,1,100uF 35V (CP_Elec_8x10),RVE100UF35V67RV0161,C2895269,Extended,5149,0.1155,JLCPCB SMT,https://www.lcsc.com/product-detail/C2895269.html
"U2,U3",2,SY8205FCC (SOIC-8-1EP_3.9x4.9mm_P1.27mm_EP2.29x3mm),Silergy SY8205FCC,C111875,Extended,10557,0.3354,JLCPCB SMT,https://www.lcsc.com/product-detail/C111875.html
"C13,C33",2,100nF (C_0603_1608Metric),CC0603KRX7R9BB104,C14663,Basic,37431294,0.006,JLCPCB SMT,https://www.lcsc.com/product-detail/C14663.html
"C15,C35",2,22nF (C_0603_1608Metric),CL10B223KB8NNNC,C21122,Basic,993844,0.0056,JLCPCB SMT,https://www.lcsc.com/product-detail/C21122.html
"L1,L2",2,4.7uH 7A (L_Sunlord_MWSA0604S),Sunlord MWSA0604S-4R7MT,C408457,Extended,8136,0.1687,JLCPCB SMT,https://www.lcsc.com/product-detail/C408457.html
"C16,C17,C18,C36,C37,C38",6,22uF 25V (C_0805_2012Metric),CL21A226MAQNNNE,C45783,Basic,4148770,0.1055,JLCPCB SMT,https://www.lcsc.com/product-detail/C45783.html
"C19,C39",2,470uF 10V (CP_Elec_6.3x7.7),RVT470UF10V67RV0159,C2858856,Extended,138705,0.0457,JLCPCB SMT,https://www.lcsc.com/product-detail/C2858856.html
"C20,C40",2,100pF (C_0603_1608Metric),CL10C101JB8NNNC,C14858,Basic,3620383,0.0082,JLCPCB SMT,https://www.lcsc.com/product-detail/C14858.html
"R11,R31",2,75k (R_0603_1608Metric),0603WAF7502T5E,C23242,Basic,725304,0.0021,JLCPCB SMT,https://www.lcsc.com/product-detail/C23242.html
"R12,R32",2,10k (R_0603_1608Metric),0603WAF1002T5E,C25804,Basic,43350791,0.0022,JLCPCB SMT,https://www.lcsc.com/product-detail/C25804.html
"R14,R34",2,12k (R_0603_1608Metric),0603WAF1202T5E,C22790,Basic,1063579,0.0031,JLCPCB SMT,https://www.lcsc.com/product-detail/C22790.html
"U4,U5,U6,U7,U8,U9",6,SY6280AAC (SOT-23-5),Silergy SY6280AAC,C55136,Extended,97877,0.089,JLCPCB SMT,https://www.lcsc.com/product-detail/C55136.html
"R51,R52,R53,R54,R55,R56",6,4.7k (R_0603_1608Metric),0603WAF4701T5E,C23162,Basic,14761704,0.0028,JLCPCB SMT,https://www.lcsc.com/product-detail/C23162.html
"C61,C62,C63,C64,C65,C66",6,10uF 25V (C_0805_2012Metric),CL21A106KAYNNNE,C15850,Basic,8632978,0.0315,JLCPCB SMT,https://www.lcsc.com/product-detail/C15850.html
"R61,R62,R63,R64,R65,R66",6,22k (R_0603_1608Metric),0603WAF2202T5E,C31850,Basic,2498475,0.0042,JLCPCB SMT,https://www.lcsc.com/product-detail/C31850.html
D2,1,Green (5 V on) (LED_0603_1608Metric),KT-0603G,C12624,Extended,296248,0.0119,JLCPCB SMT,https://www.lcsc.com/product-detail/C12624.html
R4,1,1k (R_0603_1608Metric),0603WAF1001T5E,C21190,Basic,25734337,0.0017,JLCPCB SMT,https://www.lcsc.com/product-detail/C21190.html
D3,1,Red (no PD) (LED_0603_1608Metric),KT-0603R,C2286,Basic,6051313,0.0077,JLCPCB SMT,https://www.lcsc.com/product-detail/C2286.html
R5,1,4.7k (R_0805_2012Metric),0805W8F4701T5E,C17673,Basic,4083321,0.0034,JLCPCB SMT,https://www.lcsc.com/product-detail/C17673.html
Q2,1,AO3400A (SOT-23),AOS AO3400A,C20917,Basic,918248,0.0802,JLCPCB SMT,https://www.lcsc.com/product-detail/C20917.html
J2,1,"HX TYPE C-M 16P V-SMT vertical USB-C plug (slot 1) - hand solder, see README",HX TYPE C-M 16P V-SMT,C55200592,Extended,782,0.5431,Hand solder,https://www.lcsc.com/product-detail/C55200592.html
J3,1,"HX TYPE C-M 16P V-SMT vertical USB-C plug (slot 2) - hand solder, see README",HX TYPE C-M 16P V-SMT,C55200592,Extended,782,0.5431,Hand solder,https://www.lcsc.com/product-detail/C55200592.html
J4,1,"HX TYPE C-M 16P V-SMT vertical USB-C plug (slot 3) - hand solder, see README",HX TYPE C-M 16P V-SMT,C55200592,Extended,782,0.5431,Hand solder,https://www.lcsc.com/product-detail/C55200592.html
J5,1,"HX TYPE C-M 16P V-SMT vertical USB-C plug (slot 4) - hand solder, see README",HX TYPE C-M 16P V-SMT,C55200592,Extended,782,0.5431,Hand solder,https://www.lcsc.com/product-detail/C55200592.html
J6,1,"HX TYPE C-M 16P V-SMT vertical USB-C plug (slot 5) - hand solder, see README",HX TYPE C-M 16P V-SMT,C55200592,Extended,782,0.5431,Hand solder,https://www.lcsc.com/product-detail/C55200592.html
J7,1,"HX TYPE C-M 16P V-SMT vertical USB-C plug (slot 6) - hand solder, see README",HX TYPE C-M 16P V-SMT,C55200592,Extended,782,0.5431,Hand solder,https://www.lcsc.com/product-detail/C55200592.html
—,6,"M3 x 10 mm screws, socket or pan head (from below, heads in 3 mm counterbores; 4.1 mm standoffs)",,,,,~$0.05,Off-board,https://www.amazon.com/s?k=M3+x+12mm+socket+head+screws
—,6,"M3 brass heat-set inserts, OD 4.0-4.6 mm x L 4-5.7 mm",,,,,~$0.06,Off-board,https://www.amazon.com/s?k=M3+heat+set+inserts
—,4,10 mm round rubber bumper feet (optional),,,,,~$0.05,Off-board,https://www.amazon.com/s?k=10mm+rubber+bumper+feet
—,1,"USB-C PD charger, 45 W or more (must offer 20 V >= 2.25 A or 15 V >= 3 A) + USB-C cable",,,,,~$15-25,Off-board,https://www.amazon.com/s?k=45W+USB+C+PD+charger
